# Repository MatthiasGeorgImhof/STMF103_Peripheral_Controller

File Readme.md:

Periphery contronller based F103/303 for ardupilot AP_Periph

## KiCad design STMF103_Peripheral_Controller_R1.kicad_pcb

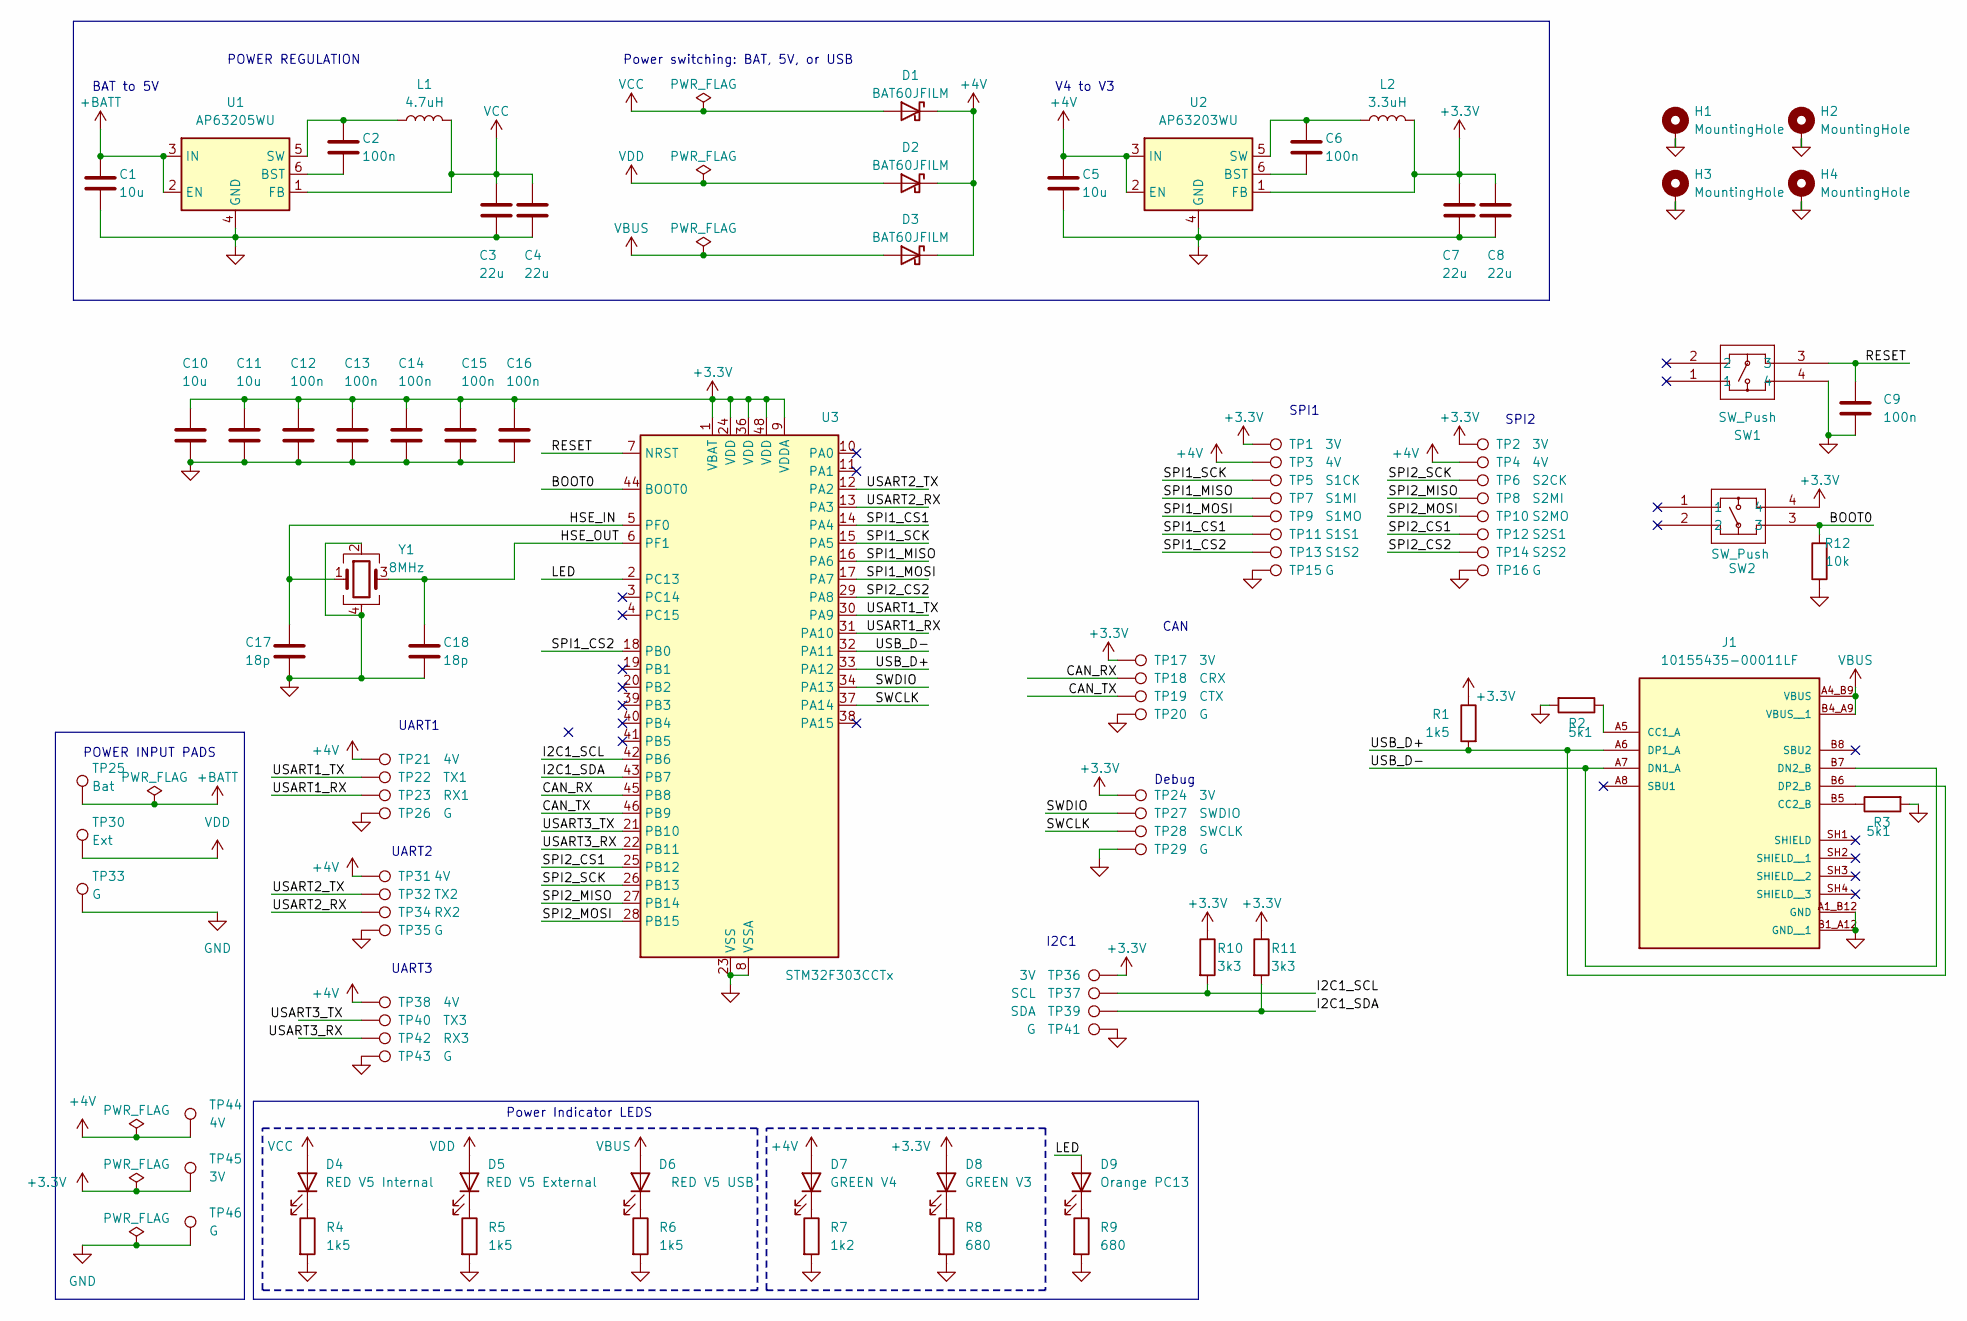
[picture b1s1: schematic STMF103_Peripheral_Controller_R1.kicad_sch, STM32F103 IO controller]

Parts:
C1, C5: 10u; C_0805_2012Metric; Voltage 50; Part Number GRM21BR61H106ME43L
C2, C6, C9, C12, C13, C14, C15, C16: 100n; C_0402_1005Metric; Voltage 16; Part Number GRM155R61C104KA88D
C3, C4, C7, C8: 22u; C_0805_2012Metric; Voltage 25; Part Number CC0805MKX5R8BB226
C10, C11: 10u; C_0603_1608Metric; Voltage 16; Part Number GRT188R61C106ME13D
C17, C18: 18p; C_0402_1005Metric; Voltage 25; Part Number CC0402JRNPO8BN180
D1, D2, D3: BAT60JFILM; D_SOD-323; Voltage 10; Part Number BAT60JFILM
D4: RED V5 Internal; LED_0603_1608Metric; Part Number LTST-C191KRKT
D5: RED V5 External; LED_0603_1608Metric; Part Number LTST-C191KRKT
D6: RED V5 USB; LED_0603_1608Metric; Part Number LTST-C191KRKT
D7: GREEN V4; LED_0603_1608Metric; Part Number LTST-C191GKT
D8: GREEN V3; LED_0603_1608Metric; Part Number LTST-C191GKT
D9: Orange PC13; LED_0603_1608Metric; Part Number LTST-C191KFKT
H1, H2, H3, H4: MountingHole; MountingHole_4.3mm_M4_Pad_Via_Custom
J1: 10155435-00011LF; AMPHENOL_10155435-00011LF; PARTREV C
L1: 4.7uH; L_1210_3225Metric; Part Number DFE322520FD-4R7M=P2
L2: 3.3uH; L_1210_3225Metric; Part Number DFE322512F-3R3M=P2
R1, R4, R5, R6: 1k5; R_0402_1005Metric; Part Number RC0402FR-071K5L
R2, R3: 5k1; R_0402_1005Metric; Part Number RC0402FR-075K1L
R7: 1k2; R_0402_1005Metric; Part Number RC0402FR-071K2L
R8, R9: 680; R_0402_1005Metric; Part Number RC0402FR-07680RL
R10, R11: 3k3; R_0402_1005Metric; Part Number RC0402FR-073K3L
R12: 10k; R_0402_1005Metric; Part Number RC0402FR-0710KL
SW1, SW2: SW_Push; EVPAA602; Part Number EVP-AA602W
TP1, TP2, TP17, TP24, TP36, TP45: 3V; TestPoint_Pad_1.5x1.5mm
TP3, TP4, TP21, TP31, TP38, TP44: 4V; TestPoint_Pad_1.5x1.5mm
TP5: S1CK; TestPoint_Pad_1.5x1.5mm
TP6: S2CK; TestPoint_Pad_1.5x1.5mm
TP7: S1MI; TestPoint_Pad_1.5x1.5mm
TP8: S2MI; TestPoint_Pad_1.5x1.5mm
TP9: S1MO; TestPoint_Pad_1.5x1.5mm
TP10: S2MO; TestPoint_Pad_1.5x1.5mm
TP11: S1S1; TestPoint_Pad_1.5x1.5mm
TP12: S2S1; TestPoint_Pad_1.5x1.5mm
TP13: S1S2; TestPoint_Pad_1.5x1.5mm
TP14: S2S2; TestPoint_Pad_1.5x1.5mm
TP15, TP16, TP20, TP26, TP29, TP35, TP41, TP43, TP46: G; TestPoint_Pad_1.5x1.5mm
TP18: CRX; TestPoint_Pad_1.5x1.5mm
TP19: CTX; TestPoint_Pad_1.5x1.5mm
TP22: TX1; TestPoint_Pad_1.5x1.5mm
TP23: RX1; TestPoint_Pad_1.5x1.5mm
TP25: Bat; TestPoint_Pad_2.0x2.0mm
TP27: SWDIO; TestPoint_Pad_1.5x1.5mm
TP28: SWCLK; TestPoint_Pad_1.5x1.5mm
TP30: Ext; TestPoint_Pad_2.0x2.0mm
TP32: TX2; TestPoint_Pad_1.5x1.5mm
TP33: G; TestPoint_Pad_2.0x2.0mm
TP34: RX2; TestPoint_Pad_1.5x1.5mm
TP37: SCL; TestPoint_Pad_1.5x1.5mm
TP39: SDA; TestPoint_Pad_1.5x1.5mm
TP40: TX3; TestPoint_Pad_1.5x1.5mm
TP42: RX3; TestPoint_Pad_1.5x1.5mm
U1: AP63205WU; TSOT-23-6; Voltage 3; Part Number AP63205WU-7
U2: AP63203WU; TSOT-23-6; Voltage 5; Part Number AP63203WU-7
U3: STM32F303CCTx; LQFP-48_7x7mm_P0.5mm; Part Number STM32F303CCT7
Y1: 8MHz; Crystal_SMD_3225-4Pin_3.2x2.5mm; Part Number ECS-80-12-33-JGN-TR

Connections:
+3.3V: C7.1, C8.1, C10.1, C11.1, C12.1, C13.1, C14.1, C15.1, C16.1, D8.2 (A), L2.2, R1.1, R10.1, R11.1, SW2.4, TP1.1, TP2.1, TP17.1, TP24.1, TP36.1, TP45.1, U2.1 (FB), U3.1 (VBAT), U3.9 (VDDA), U3.24 (VDD), U3.36 (VDD), U3.48 (VDD)
+4V: C5.1, D1.1 (K), D2.1 (K), D3.1 (K), D7.2 (A), TP3.1, TP4.1, TP21.1, TP31.1, TP38.1, TP44.1, U2.2 (EN), U2.3 (IN)
+BATT: C1.1, TP25.1, U1.2 (EN), U1.3 (IN)
/BOOT0: R12.2, SW2.3, U3.44 (BOOT0)
/CAN_RX: TP18.1, U3.45 (PB8)
/CAN_TX: TP19.1, U3.46 (PB9)
/HSE_IN: C17.1, U3.5 (PF0), Y1.1
/HSE_OUT: C18.1, U3.6 (PF1), Y1.3
/I2C1_SCL: R10.2, TP37.1, U3.42 (PB6)
/I2C1_SDA: R11.2, TP39.1, U3.43 (PB7)
/LED: D9.2 (A), U3.2 (PC13)
/RESET: C9.1, SW1.3, U3.7 (NRST)
/SPI1_CS1: TP11.1, U3.14 (PA4)
/SPI1_CS2: TP13.1, U3.18 (PB0)
/SPI1_MISO: TP7.1, U3.16 (PA6)
/SPI1_MOSI: TP9.1, U3.17 (PA7)
/SPI1_SCK: TP5.1, U3.15 (PA5)
/SPI2_CS1: TP12.1, U3.25 (PB12)
/SPI2_CS2: TP14.1, U3.29 (PA8)
/SPI2_MISO: TP8.1, U3.27 (PB14)
/SPI2_MOSI: TP10.1, U3.28 (PB15)
/SPI2_SCK: TP6.1, U3.26 (PB13)
/SWCLK: TP28.1, U3.37 (PA14)
/SWDIO: TP27.1, U3.34 (PA13)
/USART1_RX: TP23.1, U3.31 (PA10)
/USART1_TX: TP22.1, U3.30 (PA9)
/USART2_RX: TP34.1, U3.13 (PA3)
/USART2_TX: TP32.1, U3.12 (PA2)
/USART3_RX: TP42.1, U3.22 (PB11)
/USART3_TX: TP40.1, U3.21 (PB10)
/USB_D+: J1.A6 (DP1_A), J1.B6 (DP2_B), R1.2, U3.33 (PA12)
/USB_D-: J1.A7 (DN1_A), J1.B7 (DN2_B), U3.32 (PA11)
GND: C1.2, C3.2, C4.2, C5.2, C7.2, C8.2, C9.2, C10.2, C11.2, C12.2, C13.2, C14.2, C15.2, C16.2, C17.2, C18.2, H1.1, H2.1, H3.1, H4.1, J1.A1_B12 (GND), J1.B1_A12 (GND__1), R2.2, R3.2, R4.2, R5.2, R6.2, R7.2, R8.2, R9.2, R12.1, SW1.4, TP15.1, TP16.1, TP20.1, TP26.1, TP29.1, TP33.1, TP35.1, TP41.1, TP43.1, TP46.1, U1.4 (GND), U2.4 (GND), U3.8 (VSSA), U3.23 (VSS), U3.35 (VSS), U3.47 (VSS), Y1.2, Y1.4
unnamed: D4.1 (K), R4.1
unnamed: D5.1 (K), R5.1
unnamed: D6.1 (K), R6.1
unnamed: D7.1 (K), R7.1
unnamed: D8.1 (K), R8.1
unnamed: D9.1 (K), R9.1
unnamed: J1.A5 (CC1_A), R2.1
unnamed: J1.B5 (CC2_B), R3.1
unnamed: C2.2, U1.6 (BST)
unnamed: C2.1, L1.1, U1.5 (SW)
unnamed: C6.2, U2.6 (BST)
unnamed: C6.1, L2.1, U2.5 (SW)
VBUS: D3.2 (A), D6.2 (A), J1.A4_B9 (VBUS), J1.B4_A9 (VBUS__1)
VCC: C3.1, C4.1, D1.2 (A), D4.2 (A), L1.2, U1.1 (FB)
VDD: D2.2 (A), D5.2 (A), TP30.1

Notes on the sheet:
BAT to 5V
CAN
UART2
Power Indicator LEDS
SPI2
UART3
POWER INPUT PADS
POWER REGULATION
UART1
I2C1
Debug
V4 to V3
Power switching: BAT, 5V, or USB
SPI1

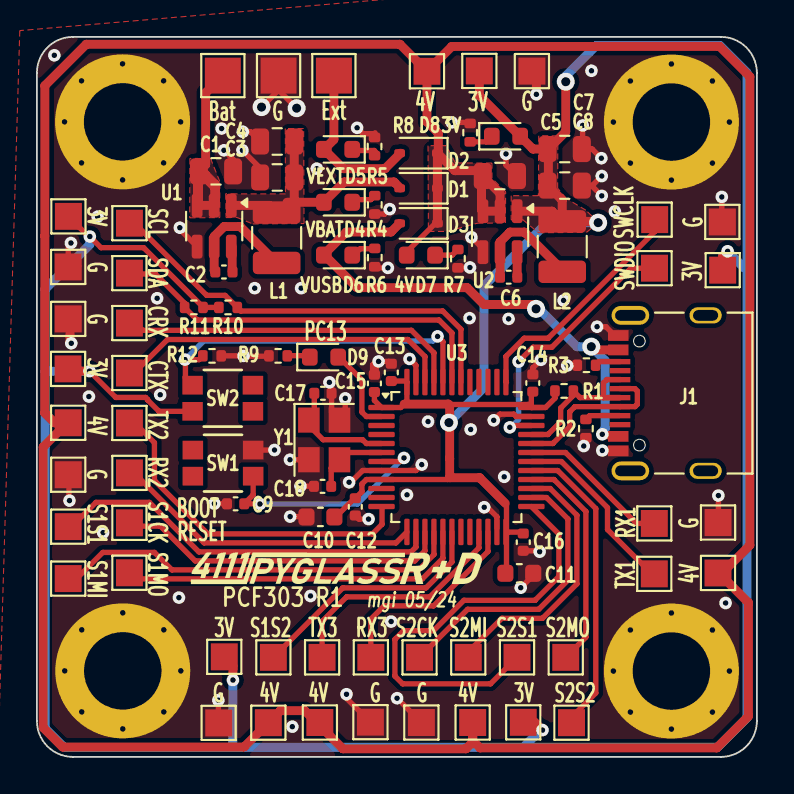
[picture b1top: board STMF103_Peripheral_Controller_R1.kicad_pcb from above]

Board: 2 copper layers, 40.0 x 40.0 mm, 98 parts (0 on the bottom side), 48 nets.

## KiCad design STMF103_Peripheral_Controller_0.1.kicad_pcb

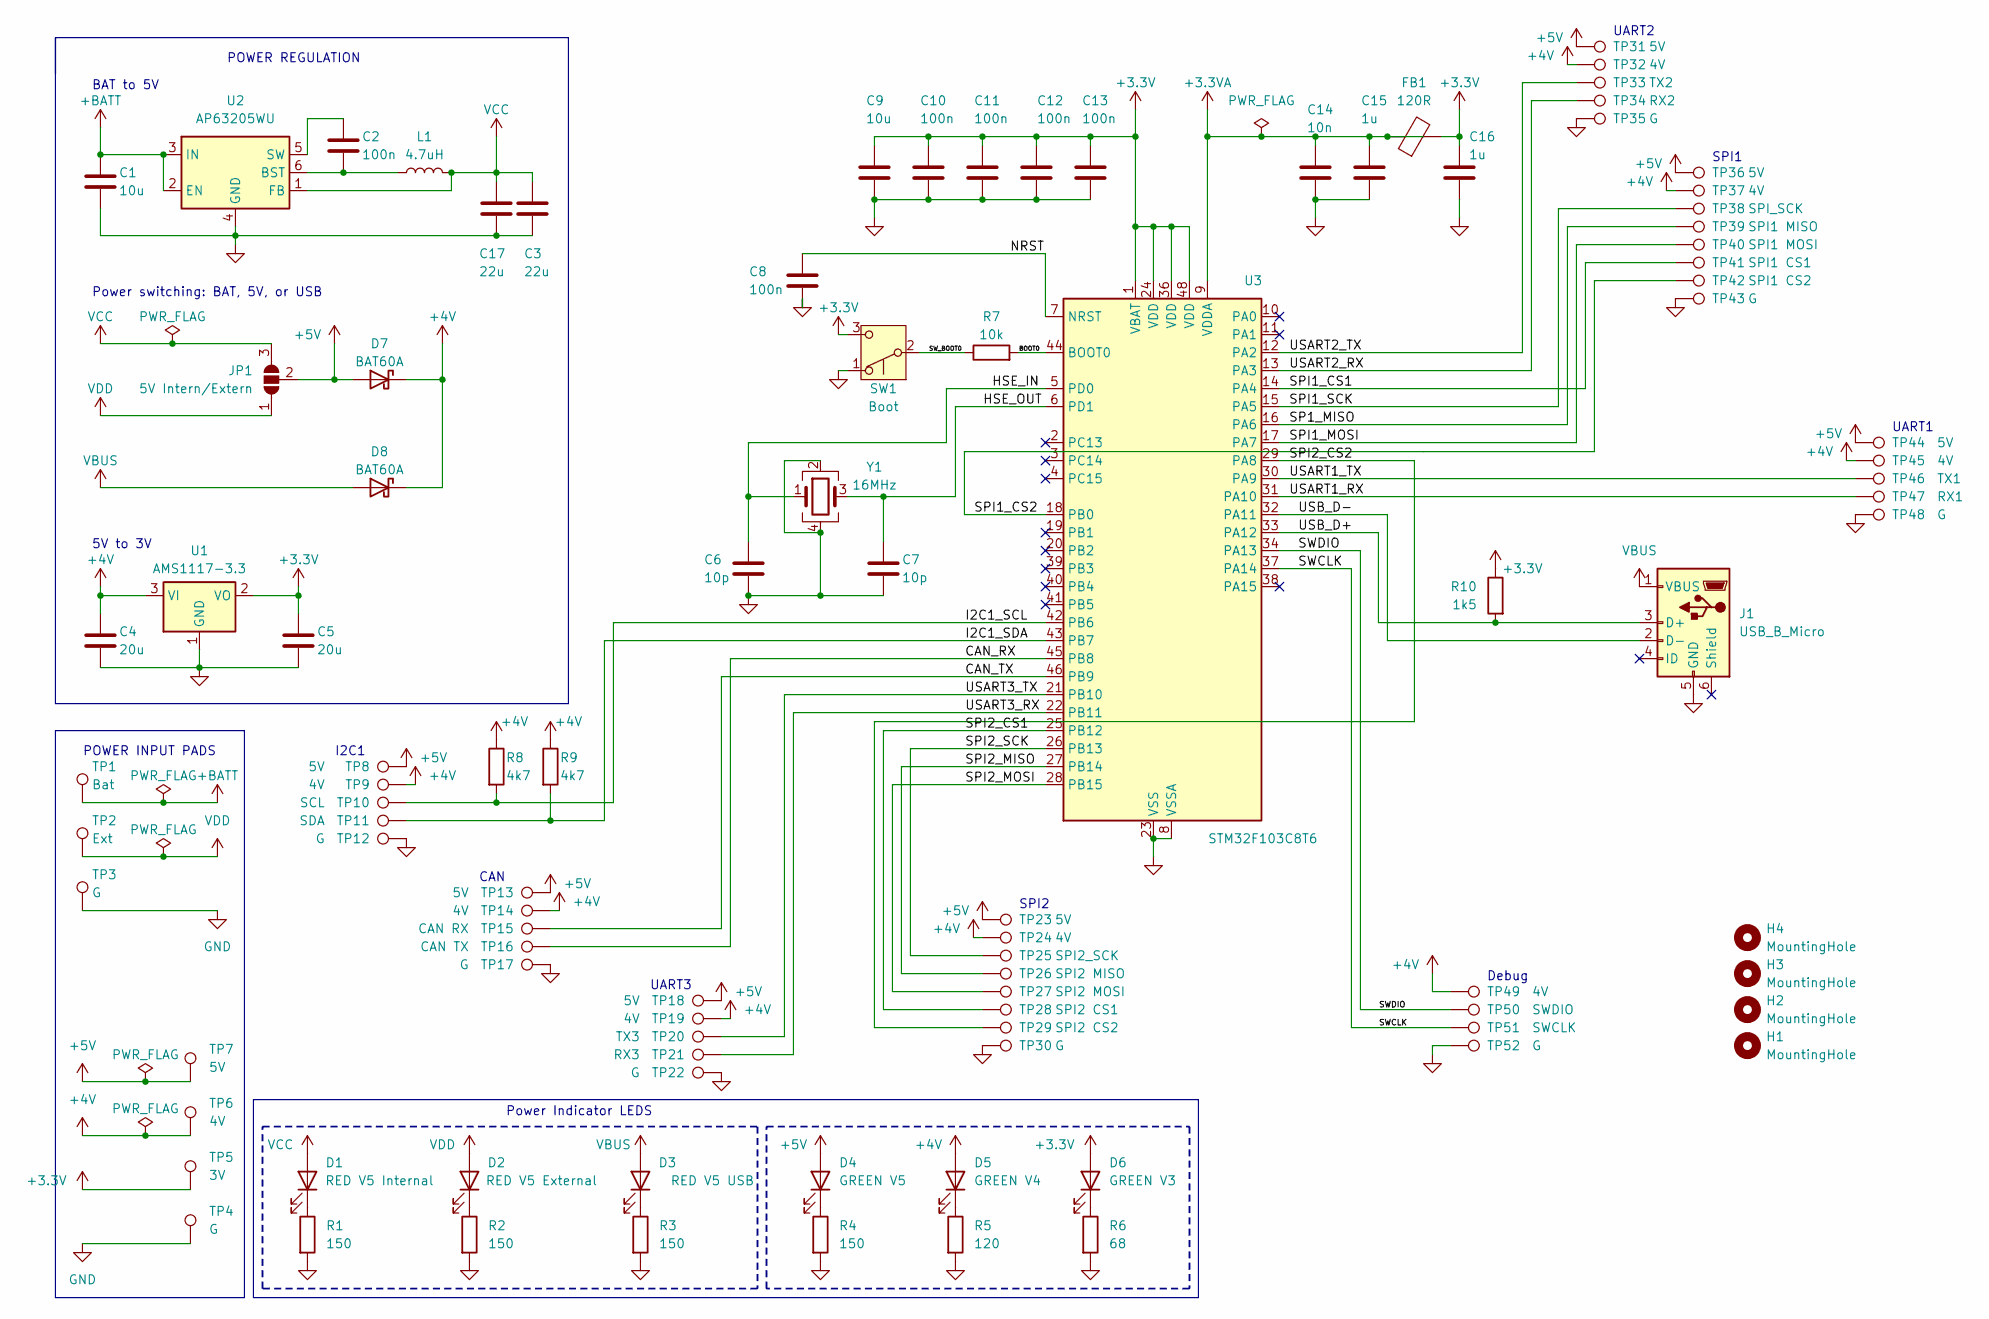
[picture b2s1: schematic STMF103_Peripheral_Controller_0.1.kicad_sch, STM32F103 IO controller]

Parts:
C1, C9: 10u; C_0603_1608Metric
C2, C8, C10, C11, C12, C13: 100n; C_0402_1005Metric
C3, C17: 22u; C_0805_2012Metric
C4, C5: 20u; C_0805_2012Metric
C6, C7: 10p; C_0402_1005Metric
C14: 10n; C_0402_1005Metric
C15, C16: 1u; C_0402_1005Metric
D1: RED V5 Internal; LED_0603_1608Metric
D2: RED V5 External; LED_0603_1608Metric
D3: RED V5 USB; LED_0603_1608Metric
D4: GREEN V5; LED_0603_1608Metric
D5: GREEN V4; LED_0603_1608Metric
D6: GREEN V3; LED_0603_1608Metric
D7, D8: BAT60A; D_SOD-323
FB1: 120R; L_0603_1608Metric
H1, H2, H3, H4: MountingHole; MountingHole_4.3mm_M4_DIN965_Pad
J1: USB_B_Micro; USB_Micro-B_Wuerth_629105150521_CircularHoles
JP1: 5V Intern/Extern; SolderJumper-3_P1.3mm_Open_Pad1.0x1.5mm
L1: 4.7uH; L_0603_1608Metric
R1, R2, R3, R4: 150; R_0402_1005Metric
R5: 120; R_0402_1005Metric
R6: 68; R_0402_1005Metric
R7: 10k; R_0402_1005Metric
R8, R9: 4k7; R_0402_1005Metric
R10: 1k5; R_0402_1005Metric
SW1: Boot; Nidec_Copal_CAS-120A
TP1: Bat; TestPoint_Pad_2.0x2.0mm
TP2: Ext; TestPoint_Pad_2.0x2.0mm
TP3: G; TestPoint_Pad_2.0x2.0mm
TP4, TP12, TP17, TP22, TP30, TP35, TP43, TP48, TP52: G; TestPoint_Pad_1.5x1.5mm
TP5: 3V; TestPoint_Pad_1.5x1.5mm
TP6, TP9, TP14, TP19, TP24, TP32, TP37, TP45, TP49: 4V; TestPoint_Pad_1.5x1.5mm
TP7, TP8, TP13, TP18, TP23, TP31, TP36, TP44: 5V; TestPoint_Pad_1.5x1.5mm
TP10: SCL; TestPoint_Pad_1.5x1.5mm
TP11: SDA; TestPoint_Pad_1.5x1.5mm
TP15: CAN RX; TestPoint_Pad_1.5x1.5mm
TP16: CAN TX; TestPoint_Pad_1.5x1.5mm
TP20: TX3; TestPoint_Pad_1.5x1.5mm
TP21: RX3; TestPoint_Pad_1.5x1.5mm
TP25: SPI2_SCK; TestPoint_Pad_1.5x1.5mm
TP26: SPI2 MISO; TestPoint_Pad_1.5x1.5mm
TP27: SPI2 MOSI; TestPoint_Pad_1.5x1.5mm
TP28: SPI2 CS1; TestPoint_Pad_1.5x1.5mm
TP29: SPI2 CS2; TestPoint_Pad_1.5x1.5mm
TP33: TX2; TestPoint_Pad_1.5x1.5mm
TP34: RX2; TestPoint_Pad_1.5x1.5mm
TP38: SPI_SCK; TestPoint_Pad_1.5x1.5mm
TP39: SPI1 MISO; TestPoint_Pad_1.5x1.5mm
TP40: SPI1 MOSI; TestPoint_Pad_1.5x1.5mm
TP41: SPI1 CS1; TestPoint_Pad_1.5x1.5mm
TP42: SPI1 CS2; TestPoint_Pad_1.5x1.5mm
TP46: TX1; TestPoint_Pad_1.5x1.5mm
TP47: RX1; TestPoint_Pad_1.5x1.5mm
TP50: SWDIO; TestPoint_Pad_1.5x1.5mm
TP51: SWCLK; TestPoint_Pad_1.5x1.5mm
U1: AMS1117-3.3; SOT-223-3_TabPin2
U2: AP63205WU; TSOT-23-6
U3: STM32F103C8T6; LQFP-48_7x7mm_P0.5mm
Y1: 16MHz; Crystal_SMD_3225-4Pin_3.2x2.5mm

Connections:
+3.3V: C5.1, C9.1, C10.1, C11.1, C12.1, C13.1, C16.1, D6.2 (A), FB1.2, R10.1, SW1.3 (C), TP5.1, U1.2 (VO), U3.1 (VBAT), U3.24 (VDD), U3.36 (VDD), U3.48 (VDD)
+3.3VA: C14.1, C15.1, FB1.1, U3.9 (VDDA)
+4V: C4.1, D5.2 (A), D7.1 (K), D8.1 (K), R8.1, R9.1, TP6.1, TP9.1, TP14.1, TP19.1, TP24.1, TP32.1, TP37.1, TP45.1, TP49.1, U1.3 (VI)
+5V: D4.2 (A), D7.2 (A), JP1.2 (C), TP7.1, TP8.1, TP13.1, TP18.1, TP23.1, TP31.1, TP36.1, TP44.1
+BATT: C1.1, TP1.1, U2.2 (EN), U2.3 (IN)
/BOOT0: R7.2, U3.44 (BOOT0)
/CAN_RX: TP16.1, U3.45 (PB8)
/CAN_TX: TP15.1, U3.46 (PB9)
/HSE_IN: C6.1, U3.5 (PD0), Y1.1
/HSE_OUT: C7.1, U3.6 (PD1), Y1.3
/I2C1_SCL: R8.2, TP10.1, U3.42 (PB6)
/I2C1_SDA: R9.2, TP11.1, U3.43 (PB7)
/NRST: C8.1, U3.7 (NRST)
/SP1_MISO: TP39.1, U3.16 (PA6)
/SPI1_CS1: TP41.1, U3.14 (PA4)
/SPI1_CS2: TP42.1, U3.18 (PB0)
/SPI1_MOSI: TP40.1, U3.17 (PA7)
/SPI1_SCK: TP38.1, U3.15 (PA5)
/SPI2_CS1: TP28.1, U3.25 (PB12)
/SPI2_CS2: TP29.1, U3.29 (PA8)
/SPI2_MISO: TP26.1, U3.27 (PB14)
/SPI2_MOSI: TP27.1, U3.28 (PB15)
/SPI2_SCK: TP25.1, U3.26 (PB13)
/SWCLK: TP51.1, U3.37 (PA14)
/SWDIO: TP50.1, U3.34 (PA13)
/SW_BOOT0: R7.1, SW1.2 (B)
/USART1_RX: TP47.1, U3.31 (PA10)
/USART1_TX: TP46.1, U3.30 (PA9)
/USART2_RX: TP34.1, U3.13 (PA3)
/USART2_TX: TP33.1, U3.12 (PA2)
/USART3_RX: TP21.1, U3.22 (PB11)
/USART3_TX: TP20.1, U3.21 (PB10)
/USB_D+: J1.3 (D+), R10.2, U3.33 (PA12)
/USB_D-: J1.2 (D-), U3.32 (PA11)
GND: C1.2, C3.2, C4.2, C5.2, C6.2, C7.2, C8.2, C9.2, C10.2, C11.2, C12.2, C13.2, C14.2, C15.2, C16.2, C17.2, J1.5 (GND), R1.2, R2.2, R3.2, R4.2, R5.2, R6.2, SW1.1 (A), TP3.1, TP4.1, TP12.1, TP17.1, TP22.1, TP30.1, TP35.1, TP43.1, TP48.1, TP52.1, U1.1 (GND), U2.4 (GND), U3.8 (VSSA), U3.23 (VSS), U3.35 (VSS), U3.47 (VSS), Y1.2, Y1.4
unnamed: D1.1 (K), R1.1
unnamed: D2.1 (K), R2.1
unnamed: D3.1 (K), R3.1
unnamed: D4.1 (K), R4.1
unnamed: D5.1 (K), R5.1
unnamed: D6.1 (K), R6.1
unnamed: C2.2, L1.1, U2.6 (BST)
unnamed: C2.1, U2.5 (SW)
VBUS: D3.2 (A), D8.2 (A), J1.1 (VBUS)
VCC: C3.1, C17.1, D1.2 (A), JP1.3 (B), L1.2, U2.1 (FB)
VDD: D2.2 (A), JP1.1 (A), TP2.1

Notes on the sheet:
BAT to 5V
CAN
Power Indicator LEDS
SPI2
UART3
POWER INPUT PADS
5V to 3V
POWER REGULATION
UART1
I2C1
Debug
Power switching: BAT, 5V, or USB
UART2
SPI1

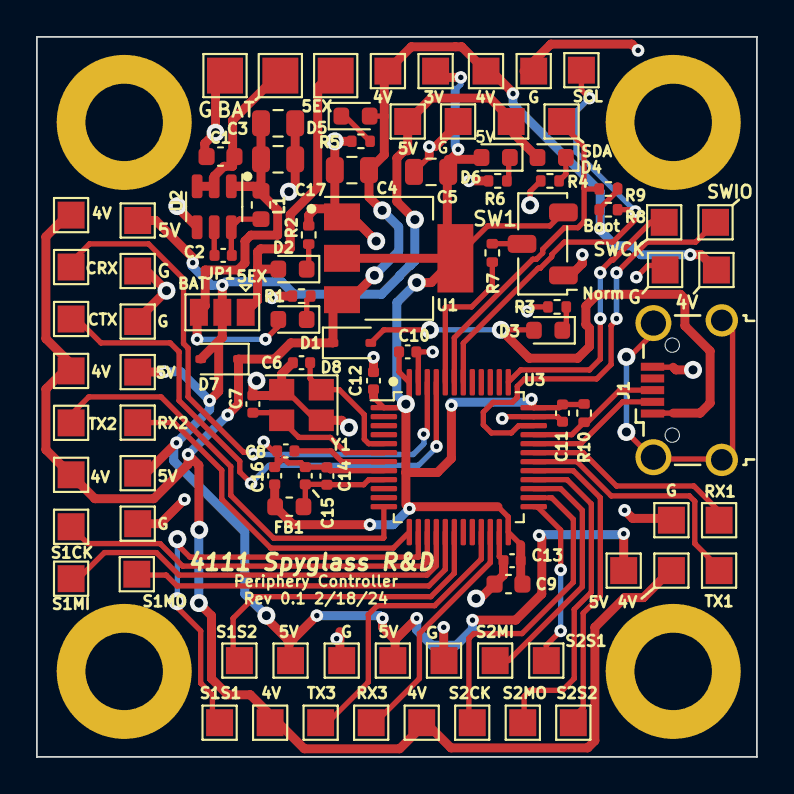
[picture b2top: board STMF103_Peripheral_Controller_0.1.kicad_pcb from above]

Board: 2 copper layers, 40.0 x 40.0 mm, 100 parts (0 on the bottom side), 46 nets.

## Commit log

2024-07-22 init repo
2024-07-22 first version based on Phils lab
2024-07-22 corrections based on PCBWAY feedback
2024-07-22 version produced by PCBWAY
2024-07-22 move step files into step3d folder
2024-07-22 some cleanup due to kicad 7 to 8, more needed
